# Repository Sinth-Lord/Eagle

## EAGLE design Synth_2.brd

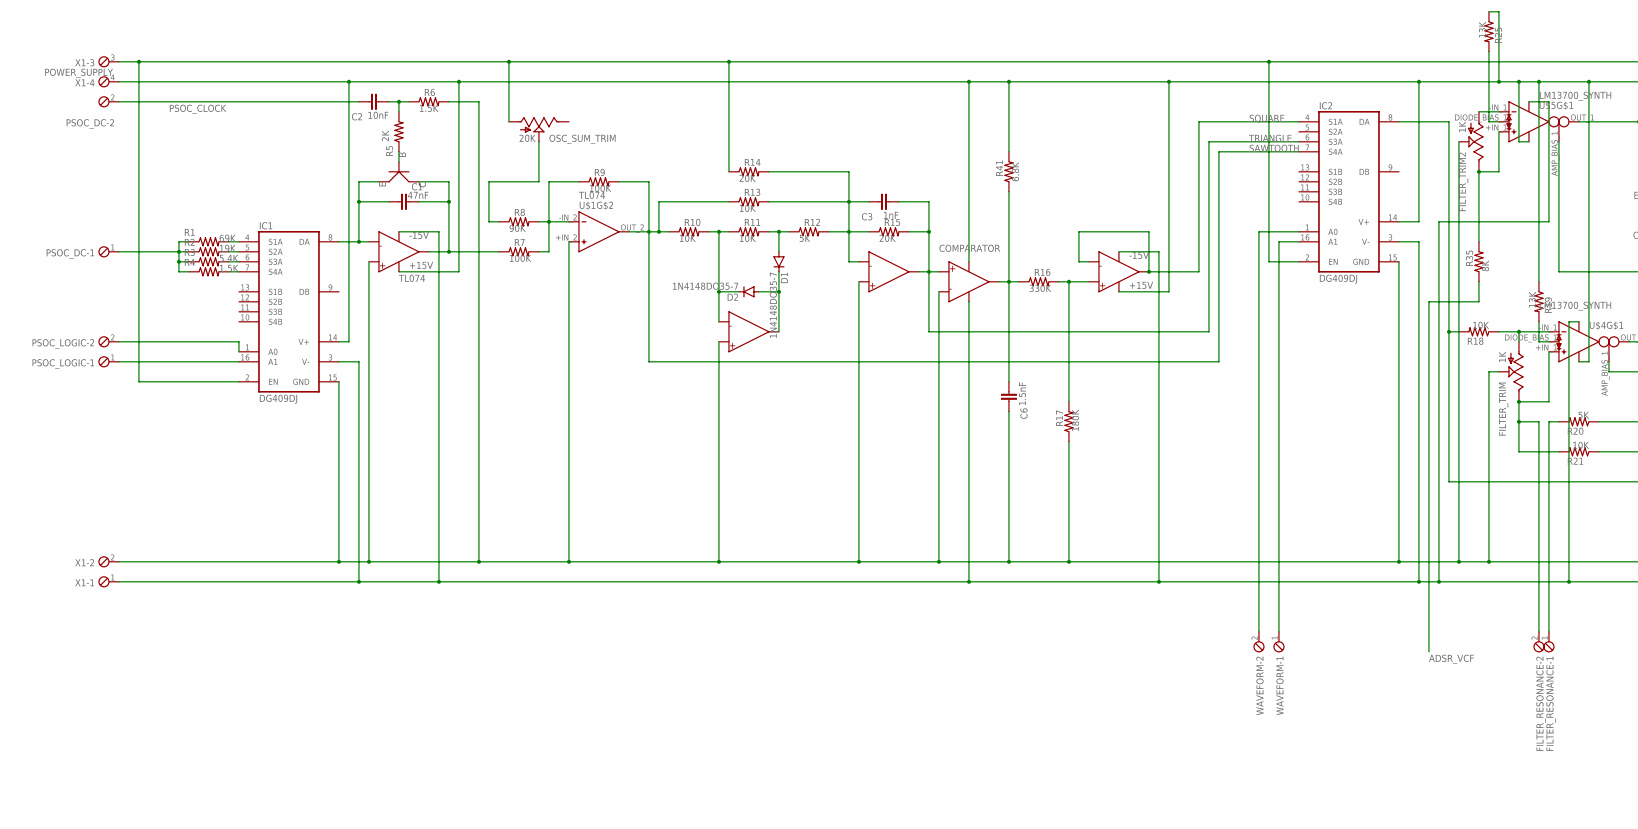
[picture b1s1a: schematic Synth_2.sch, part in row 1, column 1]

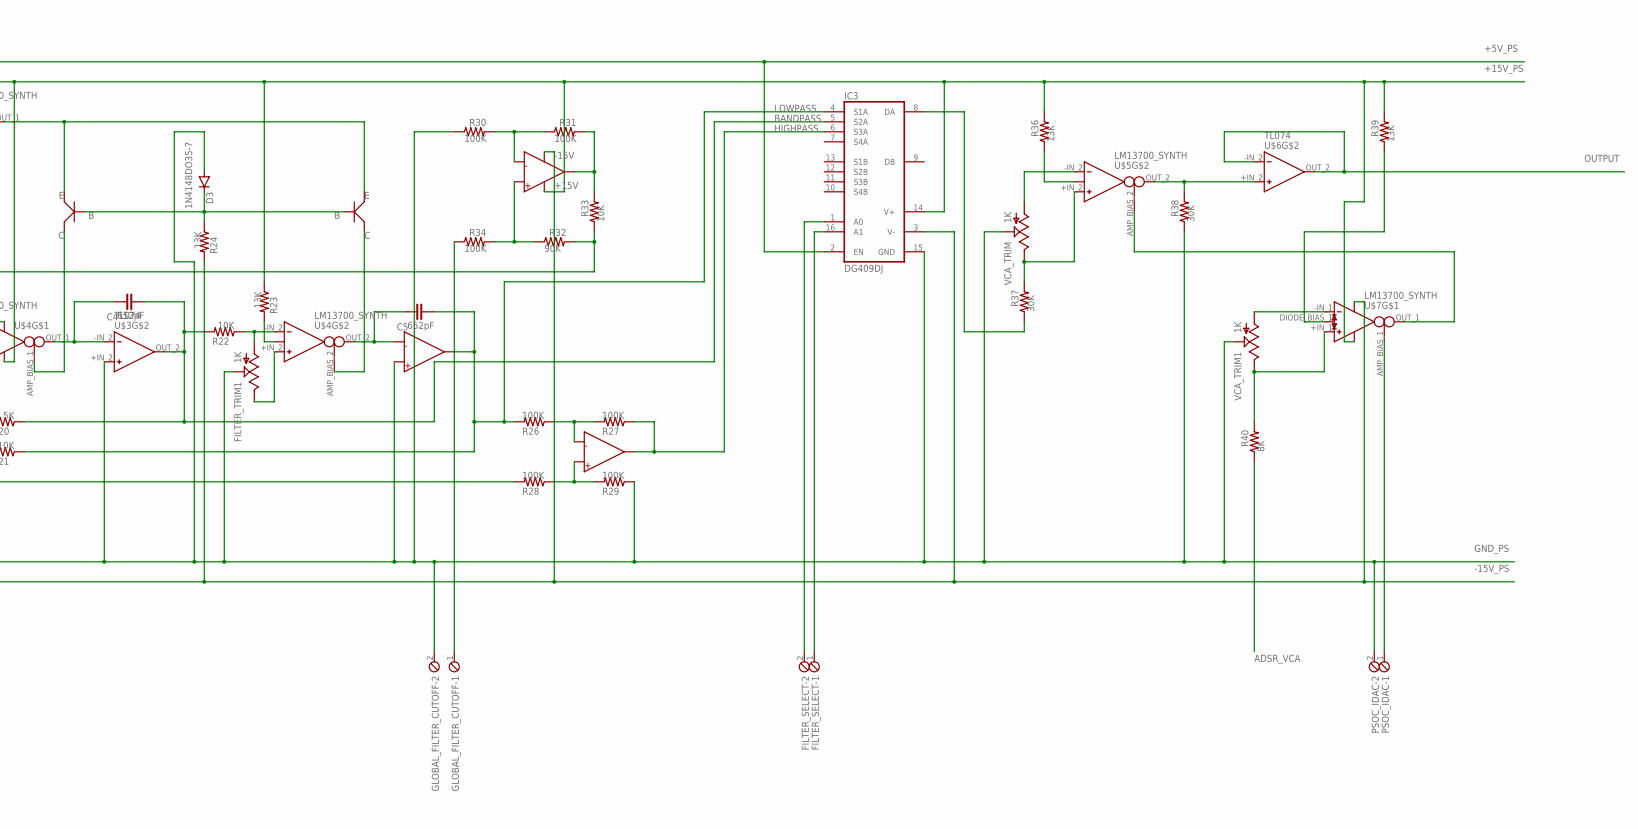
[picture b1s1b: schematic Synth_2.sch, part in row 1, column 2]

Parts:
C1, C2, C3, C4, C5, C6: C-EU025-024X044; C025-024X044
D1, D2, D3: 1N4148DO35-7; DO35-7
FILTER_RESONANCE: MPT2; 2POL254
FILTER_SELECT: MPT2; 2POL254
FILTER_TRIM, FILTER_TRIM1, FILTER_TRIM2: TRIM_US-CT6; CT6
GLOBAL_FILTER_CUTOFF: MPT2; 2POL254
IC1, IC2, IC3: DG409DJ; DIL16
LM293: LM293
OSC_SUM_TRIM: TRIM_US-CT6; CT6
PSOC_DC: MPT2; 2POL254
PSOC_IDAC: MPT2; 2POL254
PSOC_LOGIC: MPT2; 2POL254
R1, R2, R3, R4, R5, R6, R7, R8, R9, R10, R11, R12, R13, R14, R15, R16, R17, R18, R19, R20, R21, R22, R23, R24, R25, R26, R27, R28, R29, R30, R31, R32, R33, R34, R35, R36, R37, R38, R39, R40, R41: R-US_0204/7; 0204/7
U$1, U$3, U$6: TL074
U$2: MPQ2907A
U$4, U$5, U$7: LM13700_SYNTH
VCA_TRIM, VCA_TRIM1: TRIM_US-CT6; CT6
WAVEFORM: MPT2; 2POL254
X1: POWER_SUPPLY; 4POL254

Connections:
+5V_PS: IC1.2 (EN), IC2.2 (EN), IC3.2 (EN), OSC_SUM_TRIM.A, R14.1, X1.3
+15V_PS: IC1.14 (V+), IC2.14 (V+), IC3.14 (V+), LM293.VCC, R19.1, R23.1, R25.1, R36.2, R39.2, R41.2, U$1.VCC+, U$3.VCC+, U$4.+V, U$5.+V, U$6.VCC+, U$7.+V, X1.4
-15V_PS: IC1.3 (V-), IC2.3 (V-), IC3.3 (V-), LM293.GND, R24.2, U$1.VCC-, U$3.VCC-, U$4.-V, U$5.-V, U$6.VCC-, U$7.-V, X1.1
ADSR_VCA: R40.2, U$7.+IN_1, VCA_TRIM1.E
ADSR_VCF: R35.1
BANDPASS: C4.2, IC3.5 (S2A), R20.1, R22.2, U$3.OUT_2
COMPARATOR: C6.2, LM293.OUT_1, R16.1, R41.1
GND_PS: C6.1, D3.A, FILTER_TRIM.S, FILTER_TRIM1.S, FILTER_TRIM2.S, GLOBAL_FILTER_CUTOFF.2, IC1.15 (GND), IC2.15 (GND), IC3.15 (GND), LM293.-IN_1, PSOC_IDAC.2, R6.2, R17.1, R29.1, R30.1, R38.1, U$1.+IN_1, U$1.+IN_2, U$1.+IN_3, U$1.+IN_4, U$3.+IN_2, U$3.+IN_4, VCA_TRIM.S, VCA_TRIM1.S, X1.2
HIGHPASS: IC3.6 (S3A), R27.1, U$3.OUT_3
LOWPASS: C5.2, IC3.4 (S1A), R21.1, R26.2, U$3.OUT_4
unnamed: IC1.4 (S1A), R1.2
unnamed: IC1.5 (S2A), R2.2
unnamed: IC1.6 (S3A), R3.2
unnamed: IC1.7 (S4A), R4.2
unnamed: PSOC_DC.1, R1.1, R2.1, R3.1, R4.1
unnamed: IC1.1 (A0), PSOC_LOGIC.2
unnamed: IC1.16 (A1), PSOC_LOGIC.1
unnamed: R5.1, U$2.Q1_B (B)
unnamed: C2.2, R5.2, R6.1
unnamed: C1.2, R7.1, U$1.OUT_1, U$2.Q1_C (C)
unnamed: R7.2, R8.2, R9.1, U$1.-IN_2
unnamed: D2.C, R10.2, R11.1, U$1.-IN_3
unnamed: IC2.16 (A1), WAVEFORM.1
unnamed: D1.A, R11.2, R12.1
unnamed: D1.C, D2.A, U$1.OUT_3
unnamed: C3.1, R12.2, R13.2, R14.2, R15.1, U$1.-IN_4
unnamed: IC2.1 (A0), WAVEFORM.2
unnamed: IC2.8 (DA), R18.2, R28.2
unnamed: R16.2, R17.2, U$3.+IN_1
unnamed: FILTER_TRIM.A, R18.1, U$4.-IN_1
unnamed: FILTER_RESONANCE.2, FILTER_TRIM.E, R21.2, U$4.+IN_1
unnamed: R19.2, U$4.DIODE_BIAS_1
unnamed: C4.1, U$3.-IN_2, U$4.OUT_1
unnamed: U$2.Q3_C (C), U$4.AMP_BIAS_2
unnamed: FILTER_TRIM1.A, R22.1, U$4.-IN_2
unnamed: U$2.Q2_C (C), U$4.AMP_BIAS_1
unnamed: R23.2, U$4.DIODE_BIAS_2
unnamed: C5.1, U$3.-IN_4, U$4.OUT_2
unnamed: FILTER_TRIM1.E, U$4.+IN_2
unnamed: D3.C, R24.1, U$2.Q2_B (B), U$2.Q3_B (B)
unnamed: R26.1, R27.2, U$3.-IN_3
unnamed: U$2.Q2_E (E), U$2.Q3_E (E), U$5.OUT_1
unnamed: R30.2, R31.1, U$6.-IN_1
unnamed: FILTER_TRIM2.E, R35.2, U$5.+IN_1
unnamed: FILTER_TRIM2.A, U$5.-IN_1
unnamed: R25.2, U$5.DIODE_BIAS_1
unnamed: R28.1, R29.2, U$3.+IN_3
unnamed: R31.2, R33.2, U$6.OUT_1
unnamed: R32.1, R34.2, U$6.+IN_1
unnamed: R32.2, R33.1, U$5.AMP_BIAS_1
unnamed: FILTER_SELECT.1, IC3.16 (A1)
unnamed: FILTER_SELECT.2, IC3.1 (A0)
unnamed: R36.1, U$5.DIODE_BIAS_2
unnamed: GLOBAL_FILTER_CUTOFF.1, R34.1
unnamed: U$5.-IN_2, VCA_TRIM.A
unnamed: R37.2, U$5.+IN_2, VCA_TRIM.E
unnamed: U$5.AMP_BIAS_2, U$7.OUT_1
unnamed: IC3.8 (DA), R37.1
unnamed: R38.2, U$5.OUT_2, U$6.+IN_2
unnamed: PSOC_IDAC.1, U$7.AMP_BIAS_1
unnamed: R39.1, U$7.DIODE_BIAS_1
unnamed: U$7.-IN_1, VCA_TRIM1.A
unnamed: OSC_SUM_TRIM.S, R8.1
unnamed: FILTER_RESONANCE.1, R20.2
OUTPUT: U$6.-IN_2, U$6.OUT_2
PSOC_CLOCK: C2.1, PSOC_DC.2
SAWTOOTH: IC2.7 (S4A), R9.2, R10.1, R13.1, U$1.OUT_2
SQUARE: IC2.4 (S1A), U$3.-IN_1, U$3.OUT_1
TL074: C1.1, IC1.8 (DA), U$1.-IN_1, U$2.Q1_E (E)
TRIANGLE: C3.2, IC2.6 (S3A), LM293.+IN_1, R15.2, U$1.OUT_4

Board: 2 copper layers, 75 parts (0 on the bottom side), 69 nets, no tracks yet.

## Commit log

2020-03-25 Filter changes
